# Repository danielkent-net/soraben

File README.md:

# Soraben - 3D Printer BentoBox Filter Companion

Soraben is a smart device designed to allow automation of a 3D printer filter
such as the [BentoBox](https://www.printables.com/model/272525), using an
RP2040-based Raspberry Pi Pico (W) microcontroller at its core. Soraben
also includes a dedicated connector for a Sensiron SEN6x air quality sensor,
enabling both monitoring and automation of the filter, printer, or anything
else based on those sensor readins. Soraben also has optional connectors for
dual-color LED strips, and a JST-SH Qwiic-compatible connector for attaching
additional sensors, all powered through a single 24VDC input. Soraben's    
firmware is based on ESPHome, allowing its software to be upgraded, extended,
and repurposed.

More information on Soraben can be found
[on my website](https://danielkent.net/projects/posts/20260328-soraben.html).

This repository contains the KiCad design files, bill of materials, and 3D
printable enclosure for Soraben. 

# Making Your Own

Detailed fabrication and assembly instructions can be found in
[`ASSEMBLY.md`](ASSEMBLY.md).

I had my bare Soraben PCBs fabricated at [OSH Park](https://oshpark.com/). To
order at OSH Park, upload `pcb/soraben.kicad_pcb` to the OSH Park website and
follow their instructions.

For any other PCB fab, download the project files and use KiCad to generate
the Gerber files required for fabrication. You will need to add the project
symbols and footprints (both custom and the ki-lime-pi-to-go libraries)
to your project files.

I strongly suggest ordering a solder stencil and using a PCB reflow oven to
assemble the board. You can hand solder the through-hole components afterwards.

To build the firmware, use ESPHome (command line or web-based firmware builder)
to compile a `firmware.uf2` file. Then, connect the Raspberry Pi Pico W to your
computer via Micro-USB **while holding the reset button**. You can then use
`esphome upload` to automatically copy the firmware file, or you can manually
copy the generated `firmware.uf2` file to the RPI-RP2 drive on your computer.
All updates except for the initial flash can be performed over-the-air (OTA).

# License
The KiCad project files are licensed under the CERN OHL-S V2 license. You are
free to share and remix this design provided you abide by the terms of the
license, which may require you to share your design files and provide
attribution to me.

The 3D printable 3MF files are dual licensed under the CERN OHL-S V2 license
and the Creative Commons 4.0 Attribution-ShareAlike license.

The [ki-lime-pi-to-go library](https://github.com/recursivenomad/ki-lime-pi-to-go)
for Raspberry Pi Pico footprints is available from the original author under
the MIT-0 license.

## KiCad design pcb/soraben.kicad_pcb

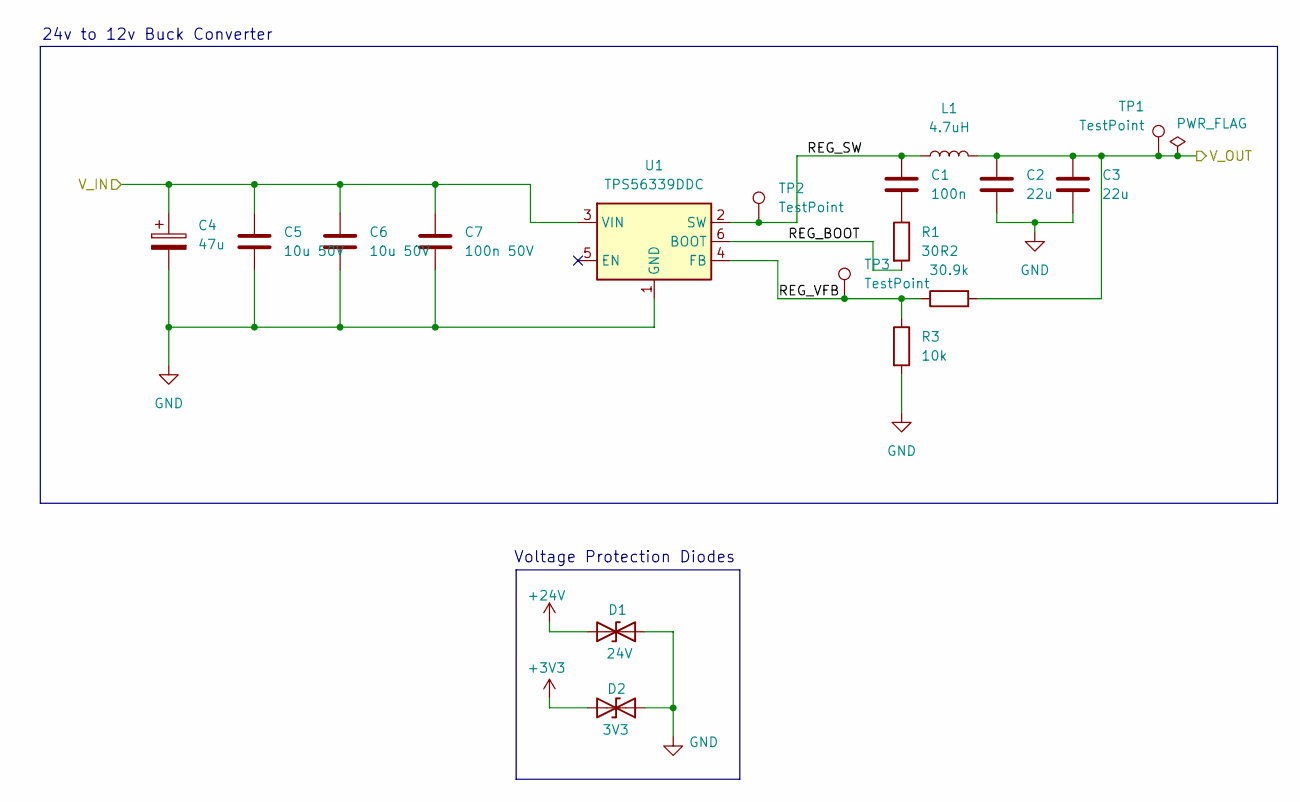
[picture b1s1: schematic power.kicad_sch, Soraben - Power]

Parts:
C1: 100n; C_0805_2012Metric
C2, C3: 22u; C_0805_2012Metric
C4: 47u; CP_Elec_6.3x7.7
C5, C6: 10u 50V; C_0805_2012Metric
C7: 100n 50V; C_0805_2012Metric
D1: 24V; D_SOD-323
D2: 3V3; D_SOD-323
L1: 4.7uH; INDPM3015X150N
R1: 30; R_0603_1608Metric
R2: 30.9k; R_0603_1608Metric
R3: 10k; R_0603_1608Metric
TP1, TP2, TP3: TestPoint; TestPoint_Pad_1.5x1.5mm
U1: TPS56339DDC; SOT-23-6

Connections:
+3V3: C2.1, C3.1, D2.2 (A2), L1.2, R2.2, TP1.1; also elsewhere on the board
+24V: C4.1, C5.1, C6.1, C7.1, D1.2 (A2), U1.3 (VIN); also elsewhere on the board
/Power/REG_BOOT: R1.2, U1.6 (BOOT)
/Power/REG_SW: C1.1, L1.1, TP2.1, U1.2 (SW)
/Power/REG_VFB: R2.1, R3.1, TP3.1, U1.4 (FB)
GND: C2.2, C3.2, C4.2, C5.2, C6.2, C7.2, D1.1 (A1), D2.1 (A1), R3.2, U1.1 (GND); also elsewhere on the board
unnamed: C1.2, R1.1

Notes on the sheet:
24v to 12v Buck Converter
Voltage Protection Diodes

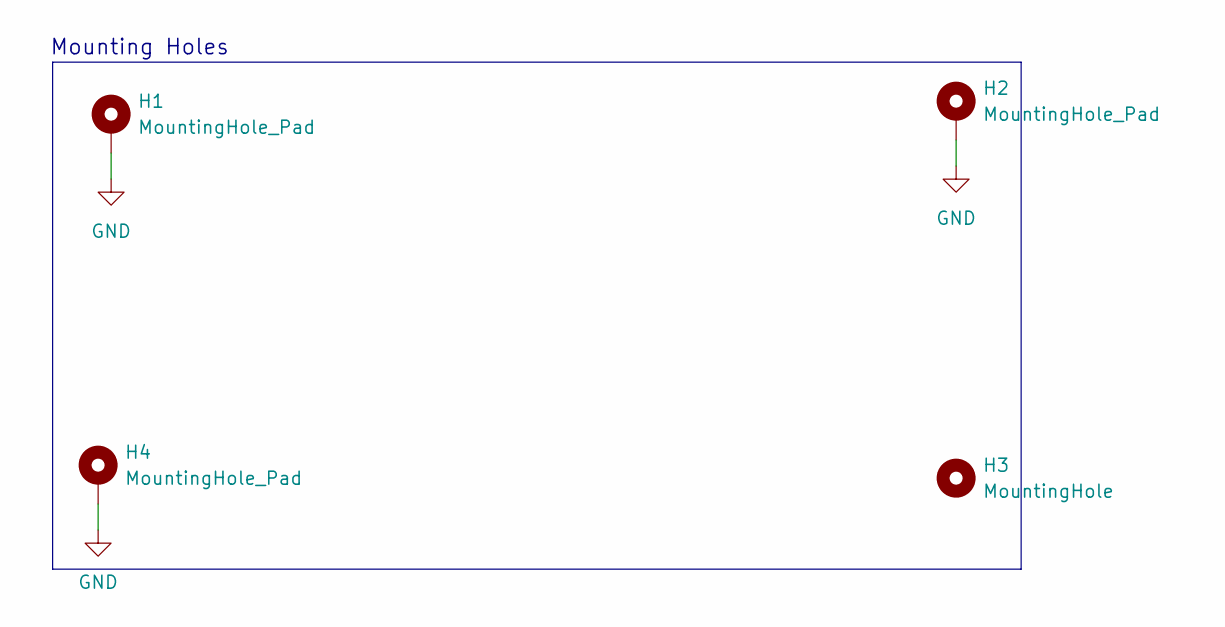
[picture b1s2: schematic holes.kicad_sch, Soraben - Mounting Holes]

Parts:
H1, H2, H4: MountingHole_Pad; MountingHole_2.2mm_M2_DIN965_Pad_TopBottom
H3: MountingHole; MountingHole_2.2mm_M2_DIN965

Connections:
GND: H1.1, H2.1, H4.1; also elsewhere on the board

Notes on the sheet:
Mounting Holes

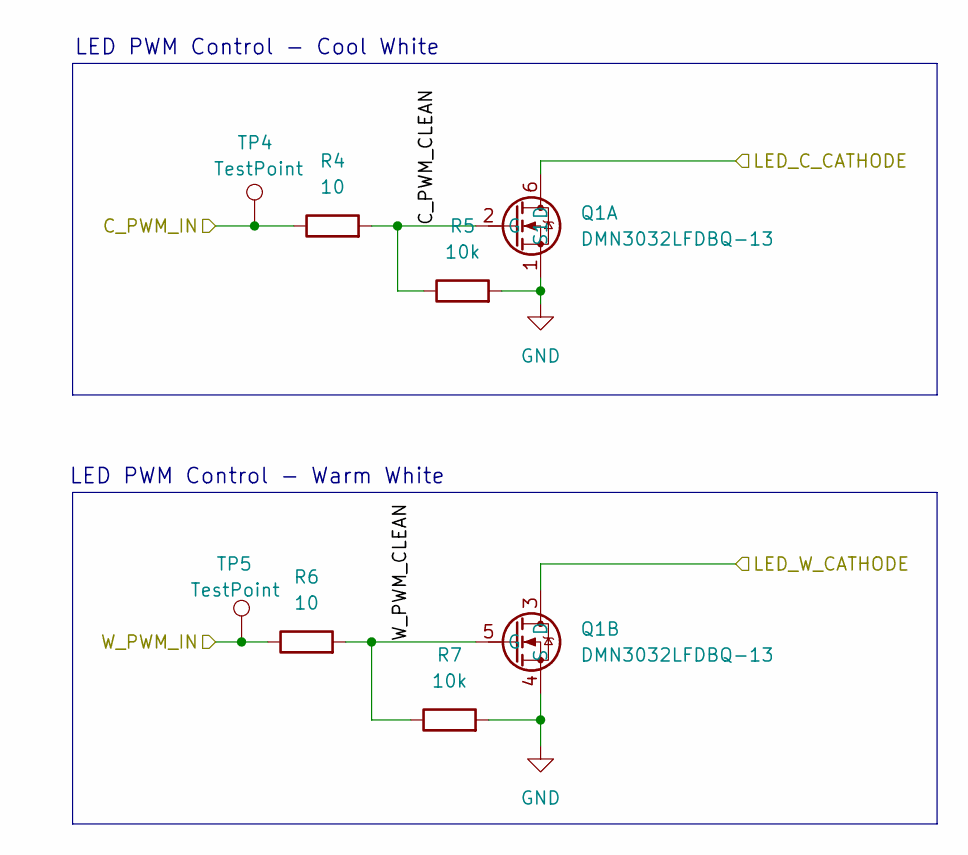
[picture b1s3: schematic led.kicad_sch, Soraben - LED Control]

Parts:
Q1: DMN3032LFDBQ-13; DMN3032LFDBQ13_OSHPark; Mouser Part Number 621-DMN3032LFDBQ-13
R4, R6: 10; R_0603_1608Metric
R5, R7: 10k; R_0603_1608Metric
TP4, TP5: TestPoint; TestPoint_Pad_1.5x1.5mm

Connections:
/LED Control/C_PWM_CLEAN: Q1.2 (G), R4.2, R5.1
/LED Control/W_PWM_CLEAN: Q1.5 (G), R6.2, R7.1
C_PWM: R4.1, TP4.1; also elsewhere on the board
GND: Q1.1 (S1), Q1.4 (S), R5.2, R7.2; also elsewhere on the board
LED_C-: Q1.6 (D); also elsewhere on the board
LED_W-: Q1.3 (D); also elsewhere on the board
W_PWM: R6.1, TP5.1; also elsewhere on the board

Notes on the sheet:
LED PWM Control - Cool White
LED PWM Control - Warm White

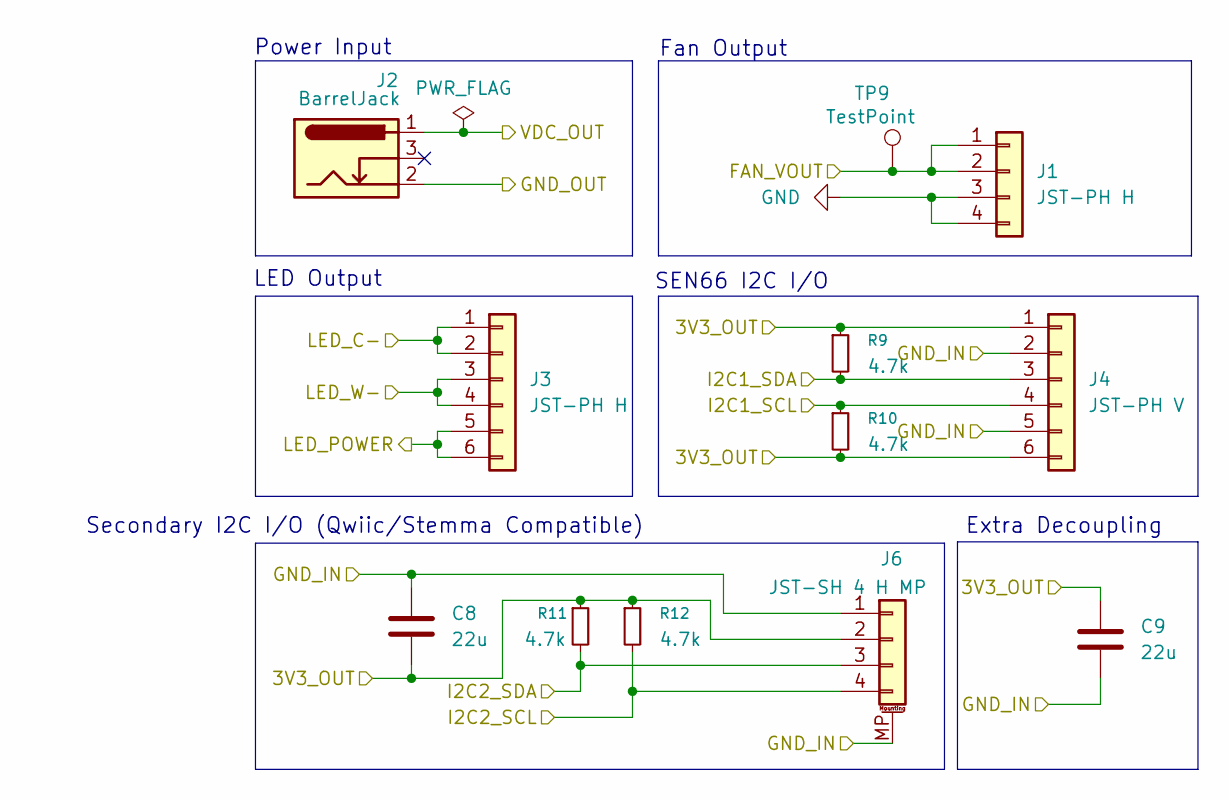
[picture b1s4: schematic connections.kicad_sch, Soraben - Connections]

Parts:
C8, C9: 22u; C_0805_2012Metric
J1: JST-PH H; JST_PH_B4B-PH-K_1x04_P2.00mm_Vertical
J2: BarrelJack; BarrelJack_Wuerth_6941xx301002_ShortOverhang
J3: JST-PH H; JST_PH_S6B-PH-K_1x06_P2.00mm_Horizontal
J4: JST-PH V; JST_PH_B6B-PH-K_1x06_P2.00mm_Vertical
J6: JST-SH 4 H MP; JST_SH_SM04B-SRSS-TB_1x04-1MP_P1.00mm_Horizontal
R9, R10, R11, R12: 4.7k; R_0603_1608Metric
TP9: TestPoint; TestPoint_Pad_1.5x1.5mm

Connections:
+3V3: C8.2, C9.1, J4.1, J4.6, J6.2, R9.1, R10.2, R11.1, R12.1; also elsewhere on the board
+24V: J2.1, J3.5, J3.6; also elsewhere on the board
FAN+: J1.1, J1.2, TP9.1; also elsewhere on the board
GND: C8.1, C9.2, J1.3, J1.4, J2.2, J4.2, J4.5, J6.1, J6.MP (MountPin); also elsewhere on the board
I2C2_SCL: J6.4, R12.2; also elsewhere on the board
I2C2_SDA: J6.3, R11.2; also elsewhere on the board
LED_C-: J3.1, J3.2; also elsewhere on the board
LED_W-: J3.3, J3.4; also elsewhere on the board
SEN_SCL: J4.4, R10.1; also elsewhere on the board
SEN_SDA: J4.3, R9.2; also elsewhere on the board

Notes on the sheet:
SEN66 I2C I/O
Extra Decoupling
LED Output
Secondary I2C I/O (Qwiic/Stemma Compatible)
Power Input
Fan Output

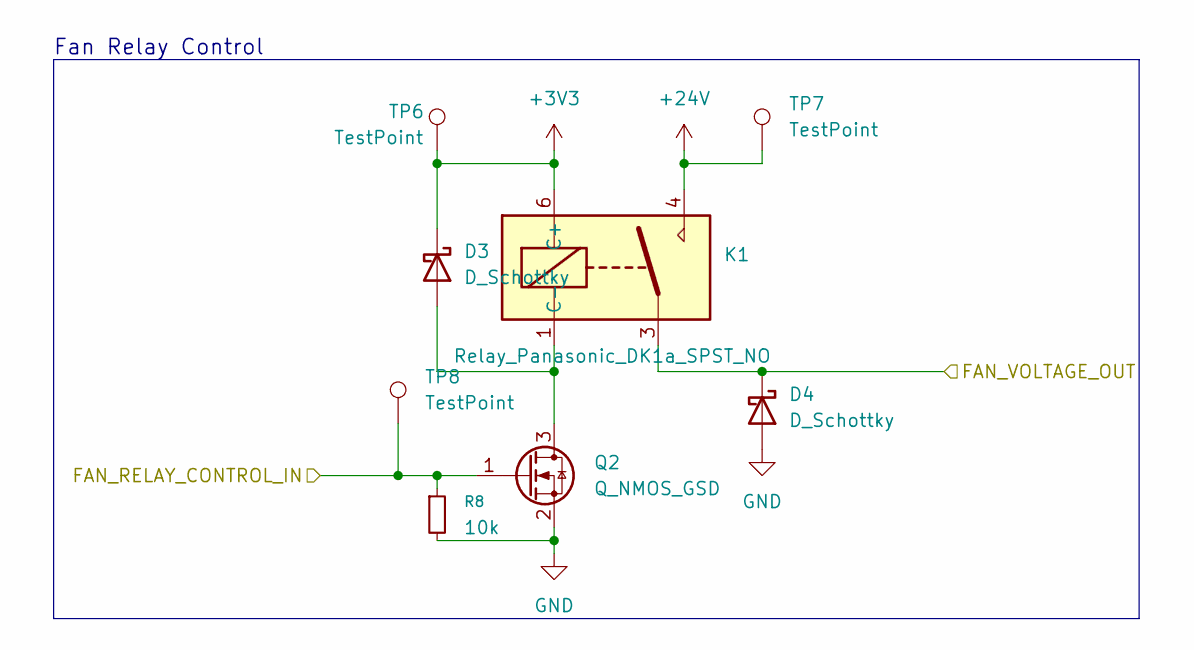
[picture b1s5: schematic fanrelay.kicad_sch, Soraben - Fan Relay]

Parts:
D3, D4: D_Schottky; D_0603_1608Metric
K1: Relay_Panasonic_DK1a_SPST_NO; Relay_SPST_Panasonic_DK_1a
Q2: Q_NMOS_GSD; SOT-323_SC-70
R8: 10k; R_0603_1608Metric
TP6, TP7, TP8: TestPoint; TestPoint_Pad_1.5x1.5mm

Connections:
+3V3: D3.1 (K), K1.6 (C+), TP6.1; also elsewhere on the board
+24V: K1.4, TP7.1; also elsewhere on the board
FAN+: D4.1 (K), K1.3; also elsewhere on the board
FAN_RELAY: Q2.1 (G), R8.1, TP8.1; also elsewhere on the board
GND: D4.2 (A), Q2.2 (S), R8.2; also elsewhere on the board
unnamed: D3.2 (A), K1.1 (C-), Q2.3 (D)

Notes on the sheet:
Fan Relay Control

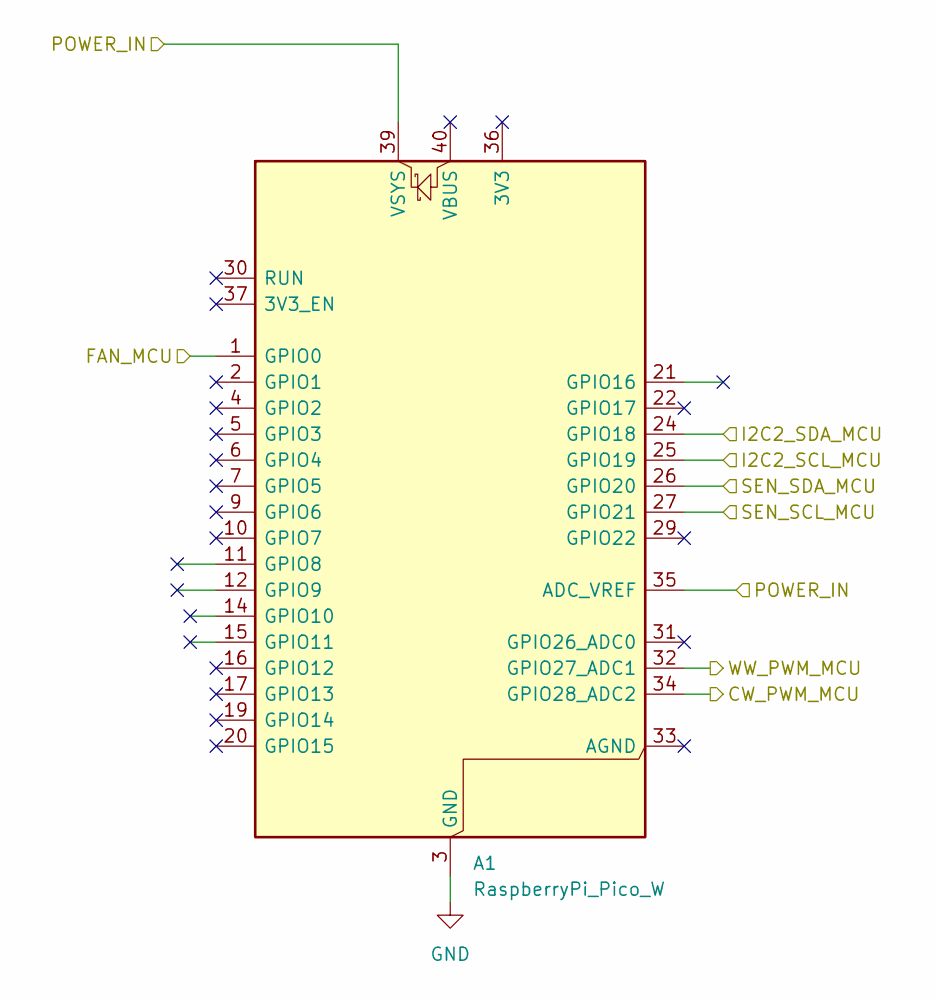
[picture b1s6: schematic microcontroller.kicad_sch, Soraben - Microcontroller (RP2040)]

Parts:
A1: RaspberryPi_Pico_W; RaspberryPi_Pico_Common_THT

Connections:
+3V3: A1.35 (ADC_VREF), A1.39 (VSYS); also elsewhere on the board
C_PWM: A1.34 (GPIO28_ADC2); also elsewhere on the board
FAN_RELAY: A1.1 (GPIO0); also elsewhere on the board
GND: A1.3 (GND), A1.8 (GND), A1.13 (GND), A1.18 (GND), A1.23 (GND), A1.28 (GND), A1.38 (GND); also elsewhere on the board
I2C2_SCL: A1.25 (GPIO19); also elsewhere on the board
I2C2_SDA: A1.24 (GPIO18); also elsewhere on the board
SEN_SCL: A1.27 (GPIO21); also elsewhere on the board
SEN_SDA: A1.26 (GPIO20); also elsewhere on the board
W_PWM: A1.32 (GPIO27_ADC1); also elsewhere on the board

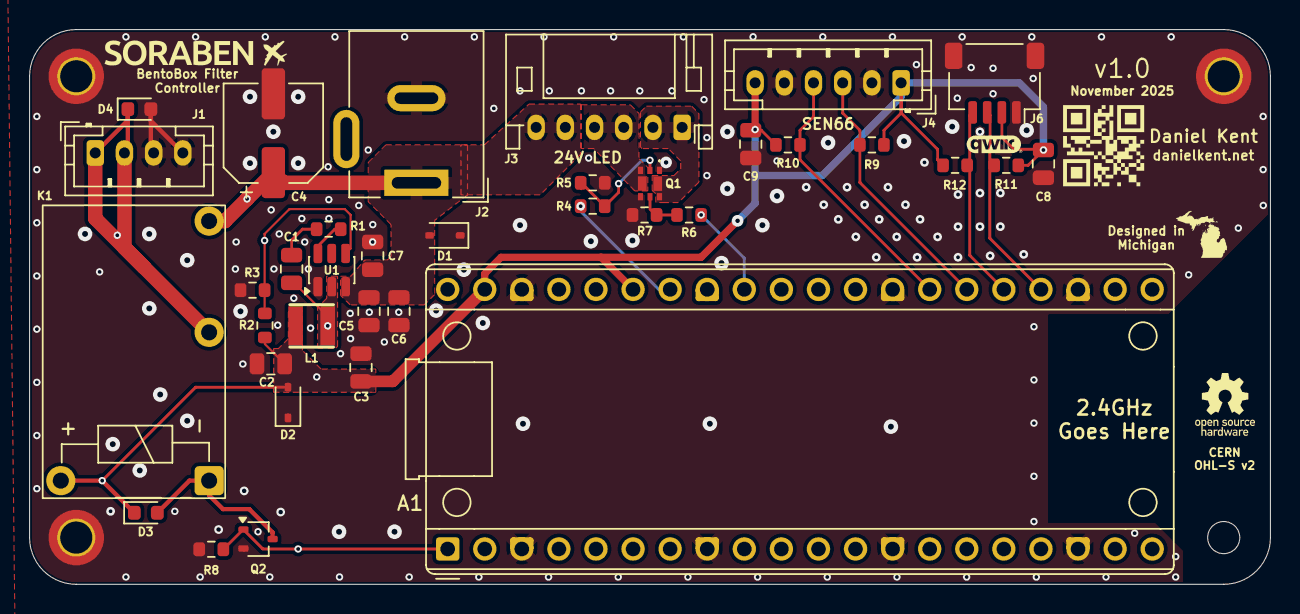
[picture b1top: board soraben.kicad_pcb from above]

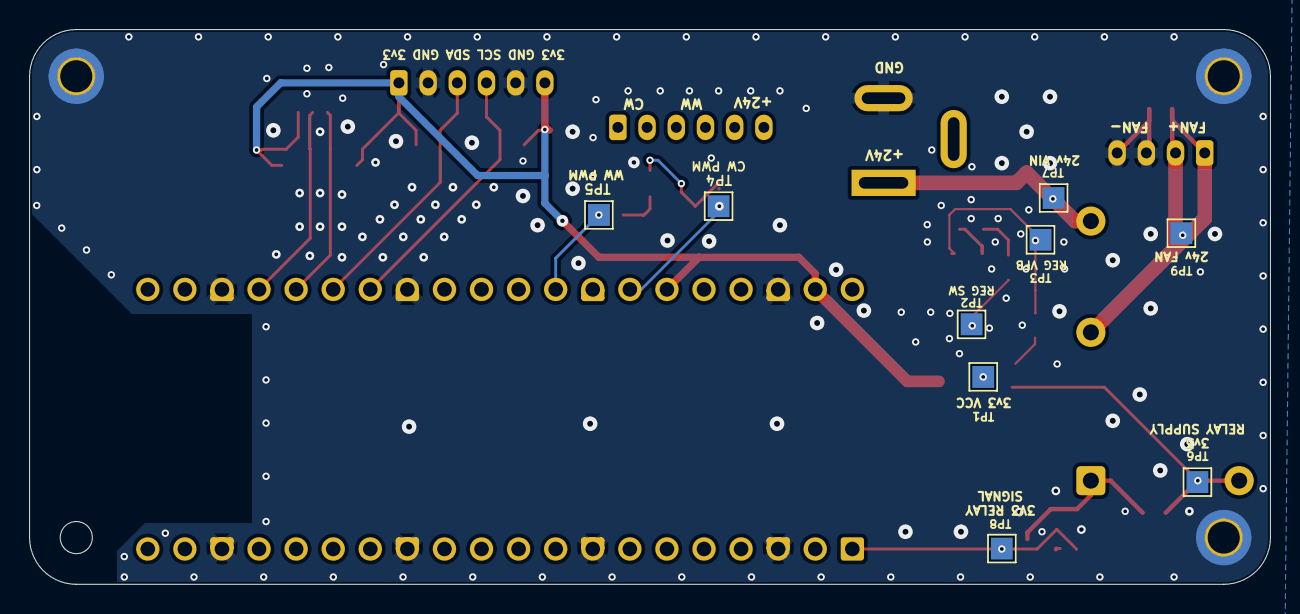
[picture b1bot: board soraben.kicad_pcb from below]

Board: 2 copper layers, 85.0 x 38.0 mm, 49 parts (9 on the bottom side), 20 nets.

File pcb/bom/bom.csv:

"Reference","Qty","Value","DNP","Exclude from BOM","Exclude from Board","Footprint","Datasheet"
"A1","1","RaspberryPi_Pico_W","","","","Module_RaspberryPi_Pico:RaspberryPi_Pico_Common_THT","https://datasheets.raspberrypi.com/picow/pico-w-datasheet.pdf"
"C1","1","100n","","","","Capacitor_SMD:C_0805_2012Metric",""
"C2,C3,C8,C9","4","22u","","","","Capacitor_SMD:C_0805_2012Metric",""
"C4","1","47u","","","","Capacitor_SMD:CP_Elec_6.3x7.7","https://www.mouser.com/datasheet/3/497/1/e_ucd.pdf"
"C5,C6","2","10u 50V","","","","Capacitor_SMD:C_0805_2012Metric",""
"C7","1","100n 50V","","","","Capacitor_SMD:C_0805_2012Metric",""
"D1","1","24V","","","","Diode_SMD:D_SOD-323",""
"D2","1","3V3","","","","Diode_SMD:D_SOD-323",""
"D3,D4","2","D_Schottky","","","","Diode_SMD:D_0603_1608Metric",""
"J1","1","JST-PH H","","","","Connector_JST:JST_PH_B4B-PH-K_1x04_P2.00mm_Vertical",""
"J2","1","BarrelJack","","","","00_Project_Footprints:BarrelJack_Wuerth_6941xx301002_ShortOverhang","https://www.mouser.com/datasheet/3/6118/1/pj_002a.pdf"
"J3","1","JST-PH H","","","","Connector_JST:JST_PH_S6B-PH-K_1x06_P2.00mm_Horizontal",""
"J4","1","JST-PH V","","","","Connector_JST:JST_PH_B6B-PH-K_1x06_P2.00mm_Vertical",""
"J6","1","JST-SH 4 H MP","","","","Connector_JST:JST_SH_SM04B-SRSS-TB_1x04-1MP_P1.00mm_Horizontal",""
"K1","1","Relay_Panasonic_DK1a_SPST_NO","","","","00_Project_Footprints:Relay_SPST_Panasonic_DK_1a",""
"L1","1","4.7uH","","","","00_Project_Footprints:INDPM3015X150N","https://www.mouser.com/datasheet/2/54/srn3015-1391515.pdf"
"Q1","1","DMN3032LFDBQ-13","","","","00_Project_Footprints:DMN3032LFDBQ13_OSHPark","https://www.diodes.com/assets/Datasheets/DMN3032LFDBQ.pdf"
"Q2","1","Q_NMOS_GSD","","","","Package_TO_SOT_SMD:SOT-323_SC-70",""
"R1","1","30","","","","Resistor_SMD:R_0603_1608Metric",""
"R2","1","30.9k","","","","Resistor_SMD:R_0603_1608Metric",""
"R3,R5,R7,R8","4","10k","","","","Resistor_SMD:R_0603_1608Metric",""
"R4,R6","2","10","","","","Resistor_SMD:R_0603_1608Metric",""
"R9,R10,R11,R12","4","4.7k","","","","Resistor_SMD:R_0603_1608Metric",""
"U1","1","TPS56339DDC","","","","Package_TO_SOT_SMD:SOT-23-6","https://www.ti.com/lit/ds/symlink/tps56339.pdf"
"SEN6X","1","SEN6X","","","","N/A (connected through cable)","https://sensirion.com/media/documents/FAFC548D/693FBB15/PS_D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"

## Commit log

2026-03-28 Add ESPHome firmware
2026-03-28 Fix linewraps in README.md
2026-03-28 Clarify symbol/footprint project library in README
2026-03-28 More clarity on firmware.
2026-03-28 Add README, LICENSE, and images
2026-03-28 Prep for Github release
2026-03-28 Add BOM csv
2026-04-26 Added PCB Stencil Jig
2026-04-26 First draft of assembly instructions
2026-04-26 Update assembly docs
2026-04-26 Add spacing to component order
2026-04-26 Add Assembly Instructions
    Added more detailed assembly instructions to the repository in a separate document

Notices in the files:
pcb/connections.kicad_sch:
CERN OHL-S v2.0
